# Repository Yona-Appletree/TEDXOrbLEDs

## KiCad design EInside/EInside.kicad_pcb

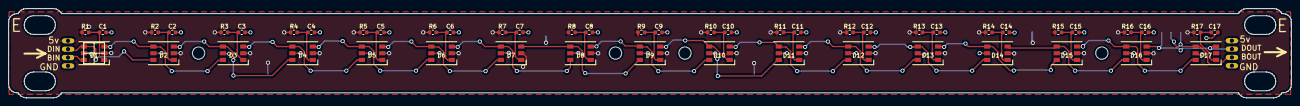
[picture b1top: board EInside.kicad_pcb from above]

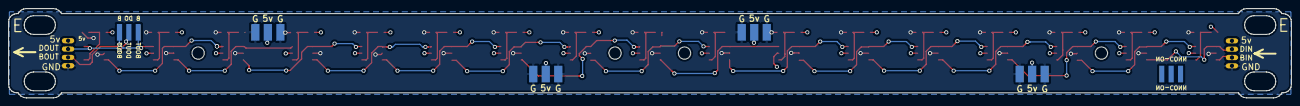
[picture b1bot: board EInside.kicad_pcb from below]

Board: 2 copper layers, 307.7 x 21.4 mm, 59 parts (6 on the bottom side), 38 nets.

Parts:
C1, C2, C3, C4, C5, C6, C7, C8, C9, C10, C11, C12, C13, C14, C15, C16, C17: .1uF; C_0603_1608Metric
D1, D2, D3, D4, D5, D6, D7, D8, D9, D10, D11, D12, D13, D14, D15, D16, D17: WS2813; LED_WS2812_PLCC6_5.0x5.0mm_P1.6mm
J1: IN; TEDX_INNER_4
J3, J3#2, J3#3, J3#4: PWR_BRIDGE; TEDX_PWR_BRIDGE_TALL
J4, J4#2: DAT_BRIDGE; TEDX_DAT_BRIDGE_TALL
J5: OUT; TEDX_INNER_4
R1, R2, R3, R4, R5, R6, R7, R8, R9, R10, R11, R12, R13, R14, R15, R16, R17: 330; R_0603_1608Metric

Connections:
+5V: D1.2, D2.2, D3.2, D4.2, D5.2, D6.2, D7.2, D8.2, D9.2, D10.2, D11.2, D12.2, D13.2, D14.2, D15.2, D16.2, D17.2, J1.1, J3.1, J3#2.1, J3#3.1, J3#4.1, J5.1, R1.1, R2.1, R3.1, R4.1, R5.1, R6.1, R7.1, R8.1, R9.1, R10.1, R11.1, R12.1, R13.1, R14.1, R15.1, R16.1, R17.1
/BIN: D1.6, J1.3
/BOUT: D16.3, D17.4, J4#2.2, J5.3
/DIN: D1.4, D2.6, J1.2
/DOUT: D17.3, J4#2.1, J5.2
GND: C1.2, C2.2, C3.2, C4.2, C5.2, C6.2, C7.2, C8.2, C9.2, C10.2, C11.2, C12.2, C13.2, C14.2, C15.2, C16.2, C17.2, D1.5, D2.5, D3.5, D4.5, D5.5, D6.5, D7.5, D8.5, D9.5, D10.5, D11.5, D12.5, D13.5, D14.5, D15.5, D16.5, D17.5, J1.4, J3.2, J3#2.2, J3#3.2, J3#4.2, J5.4
unnamed: C1.1, D1.1, R1.2
unnamed: C2.1, D2.1, R2.2
unnamed: C3.1, D3.1, R3.2
unnamed: C4.1, D4.1, R4.2
unnamed: C5.1, D5.1, R5.2
unnamed: C6.1, D6.1, R6.2
unnamed: C7.1, D7.1, R7.2
unnamed: C8.1, D8.1, R8.2
unnamed: C9.1, D9.1, R9.2
unnamed: C10.1, D10.1, R10.2
unnamed: C11.1, D11.1, R11.2
unnamed: C12.1, D12.1, R12.2
unnamed: C13.1, D13.1, R13.2
unnamed: C14.1, D14.1, R14.2
unnamed: C15.1, D15.1, R15.2
unnamed: C16.1, D16.1, R16.2
unnamed: C17.1, D17.1, R17.2
unnamed: D1.3, D2.4, D3.6
unnamed: D2.3, D3.4, D4.6
unnamed: D3.3, D4.4, D5.6
unnamed: D4.3, D5.4, D6.6
unnamed: D5.3, D6.4, D7.6
unnamed: D6.3, D7.4, D8.6
unnamed: D7.3, D8.4, D9.6
unnamed: D10.3, D11.4, D12.6
unnamed: D9.3, D10.4, D11.6
unnamed: D8.3, D9.4, D10.6
unnamed: D11.3, D12.4, D13.6
unnamed: D12.3, D13.4, D14.6
unnamed: D13.3, D14.4, D15.6
unnamed: D14.3, D15.4, D16.6
unnamed: D15.3, D16.4, D17.6

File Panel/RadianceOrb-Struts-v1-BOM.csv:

Item #,*Ref Des,*Qty,Manufacturer,*Mfg Part #,Description / Value,*Package,Type,Your Instructions / Notes
1,"R1,R2,R3,R4,R5,R6,R7,R8,R9,R10,R11,R12,R13,R14,R15,R16,R17",214,Generic,-,RES 330 OHM 1/8W 1% 0805 SMD,0805,SMD,
1,"C1,C2,C3,C4,C5,C6,C7,C8,C9,C10,C11,C12,C13,C14,C15,C16,C17",214,Generic,-,CAP CER 100nF 16V 10% X7R 0805,0805,SMD,
1,"D1,D2,D3,D4,D5,D6,D7,D8,D9,D10,D11,D12,D13,D14,D15,D16,D17",214,Generic,-,ADDRESS LED DISCRETE SERIAL RGB,5050,SMD,

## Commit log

2019-02-17 Initial WIP commit
2019-02-17 First iteration of all struts
2019-05-01 Second Prototypes
2019-05-07 Second Prototype Run
2019-05-12 Before changing Outside Struts to not have connectors
2019-05-30 Prototype v4
